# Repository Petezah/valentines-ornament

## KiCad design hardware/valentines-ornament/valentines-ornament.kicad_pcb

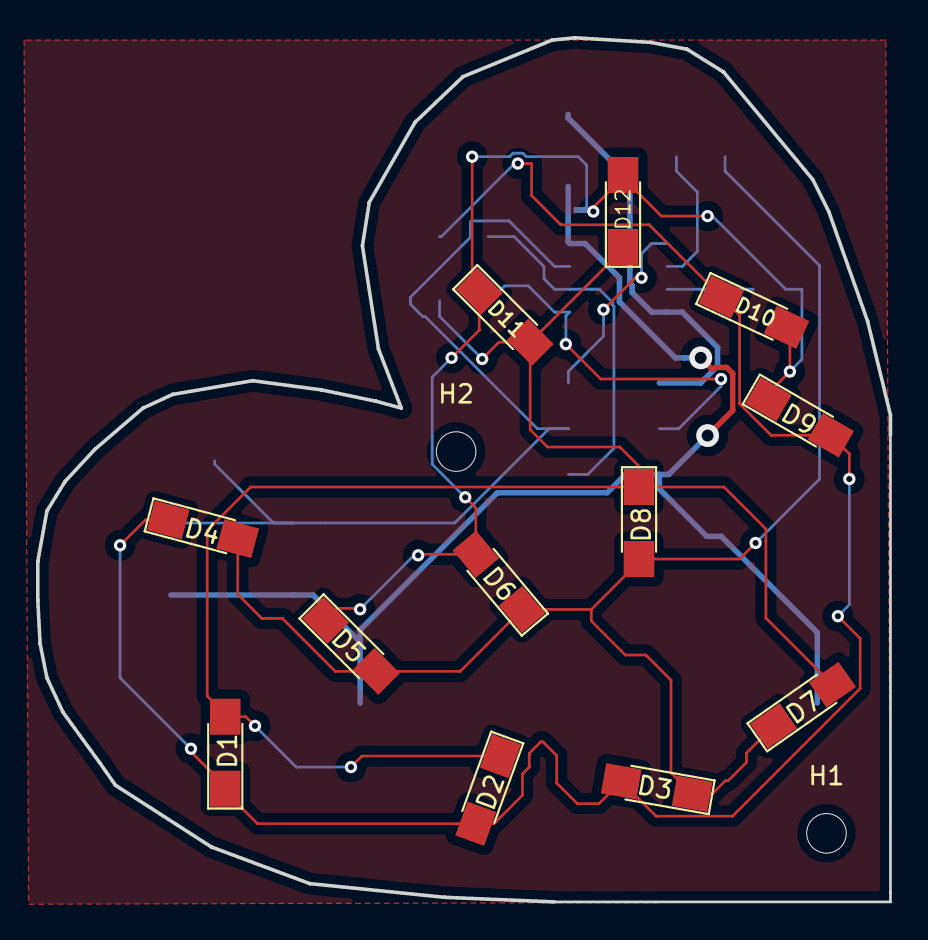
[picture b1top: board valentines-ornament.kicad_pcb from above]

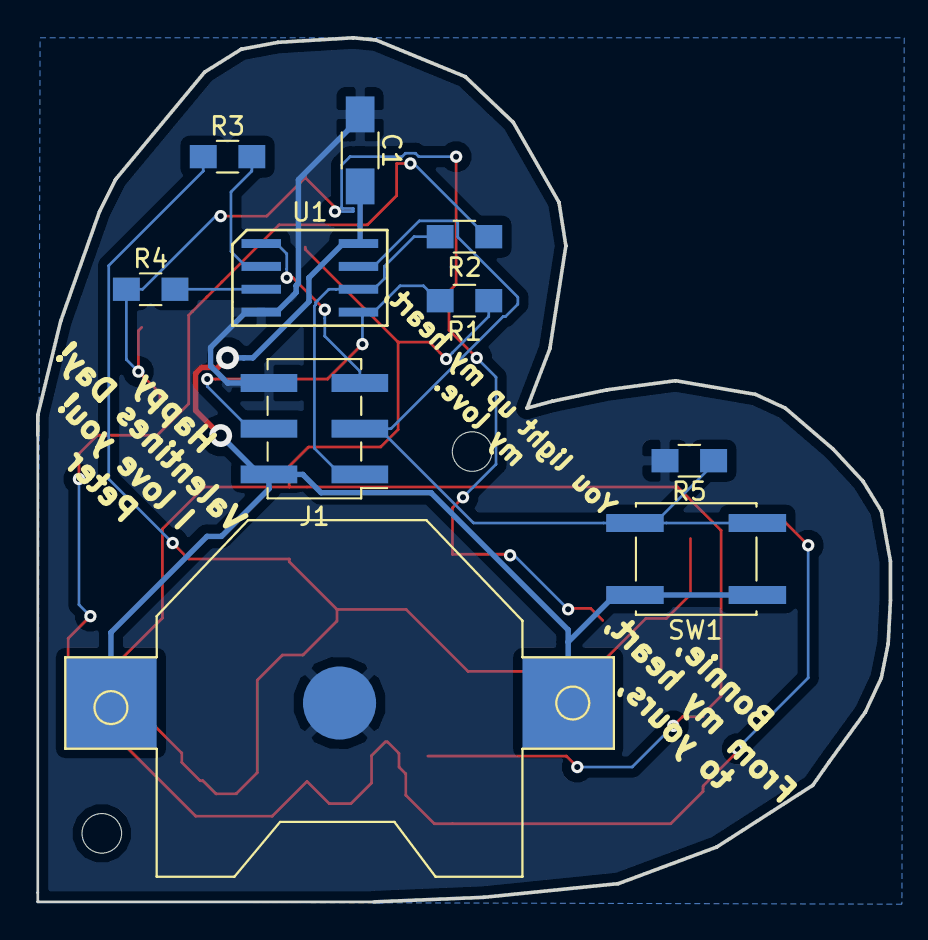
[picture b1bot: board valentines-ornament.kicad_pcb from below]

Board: 2 copper layers, 47.4 x 48.0 mm, 25 parts (10 on the bottom side), 12 nets.

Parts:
BT1: Battery_Cell; CR2032-SMD
C1: 10uF; C_1206_HandSoldering
D1, D2, D3, D4, D5, D6, D7, D8, D9, D10, D11, D12: LED; LED_1206_HandSoldering
G1: mask-symbol; abstract-heart
H1, H2: MountingHole; MountingHole_2.2mm_M2
J1: AVR-ISP-6; Pin_Header_Straight_2x03_Pitch2.54mm_SMD
R1, R2, R3, R4: 270; R_0805_HandSoldering
R5: 10K; R_0805_HandSoldering
SW1: SW_Push; SW_SPST_EVQQ2
U1: ATtiny85-20SU; SOIJ-8_5.3x5.3mm_P1.27mm

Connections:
+3V3: BT1.1, C1.2, J1.2, SW1.1, U1.8
/MISO: J1.1, R2.2, U1.6
/MOSI: J1.4, R1.2, U1.5
/RST: J1.5, U1.1
/SCK_BUTTON: J1.3, R5.1, SW1.2, U1.7
GND: BT1.2, C1.1, J1.6, R5.2, U1.4
unnamed: D1.1, D2.2, D3.2, D4.1, D9.2, D10.1, R2.1
unnamed: D1.2, D2.1, D7.2, D8.1, D11.2, D12.1, R1.1
unnamed: D3.1, D4.2, D5.2, D6.1, D7.1, D8.2, R3.1
unnamed: D5.1, D6.2, D9.1, D10.2, D11.1, D12.2, R4.1
unnamed: R3.2, U1.2
unnamed: R4.2, U1.3

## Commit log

2019-02-03 Set up 4 wire (12 LED) charlieplex circuit, and ATTiny85 (not connected yet)
2019-02-03 Add backup file to gitignore
2019-02-03 Finished schematic capture; started PCB layout
2019-02-04 Add battery cell
2019-02-05 Add heart solder mask logo, switch resistors to 0805
2019-02-05 Position all the parts
2019-02-05 Tweak layout
2019-02-05 Finish placing
2019-02-05 Finished routing
2019-02-05 Add some text
2019-02-20 Simple charlieplex firmware
2019-02-21 Fix firmware and make it more interesting also
